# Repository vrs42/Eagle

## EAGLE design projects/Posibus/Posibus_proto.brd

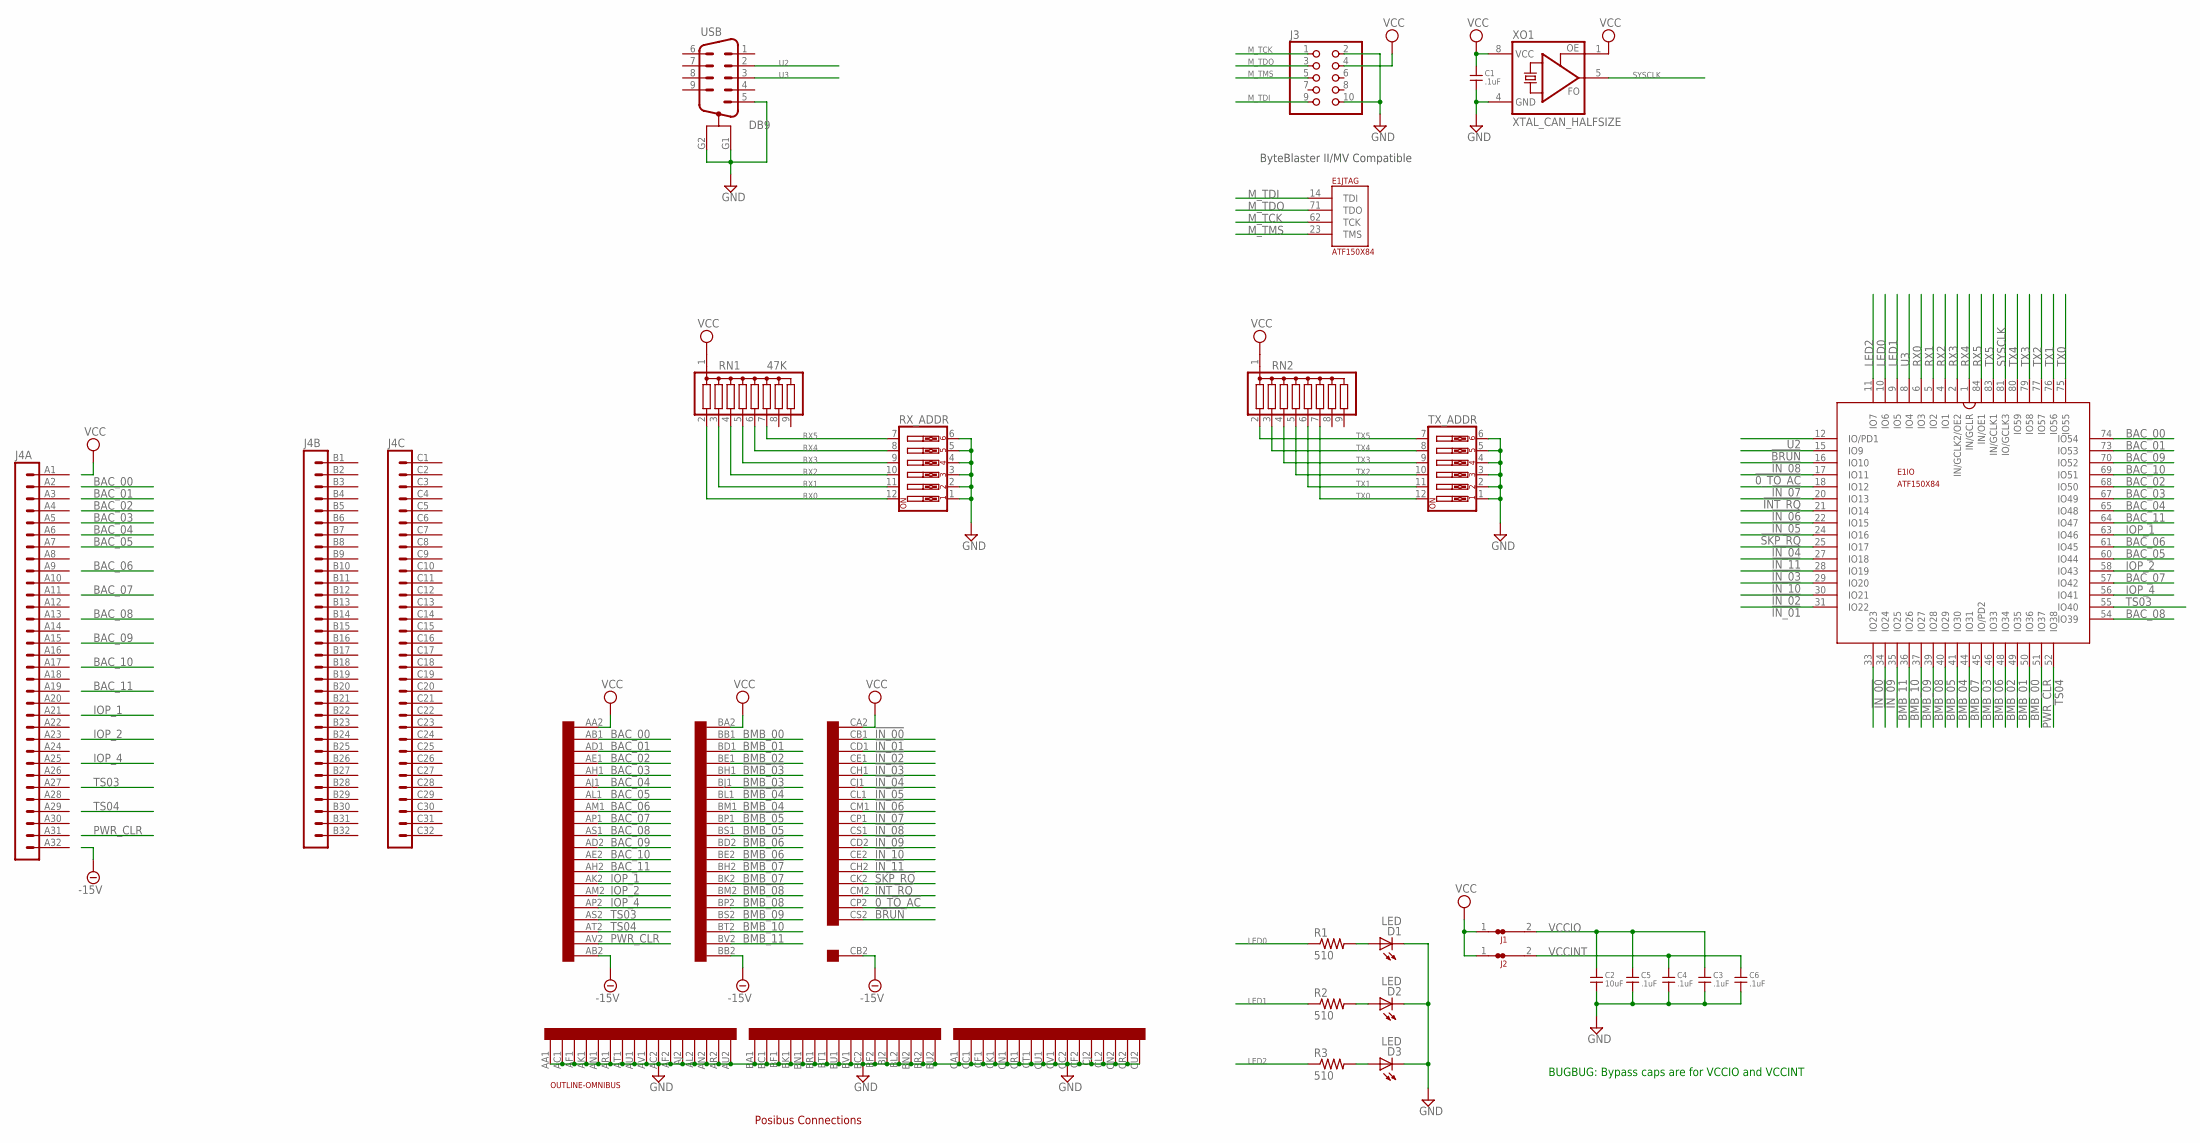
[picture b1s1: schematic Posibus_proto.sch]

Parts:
C1, C3, C4, C5, C6: .1uF; C_TH_5MM
C2: 10uF; C_TH_5MM
D1, D2, D3: LED; LED_TH_3MM
E1: ATF150X84; S84
J1, J2: JUMPER-NC1; NC1
J3: HDR_2X5"; HDR_2X5
J4: VG96-3B; VG96B
R1, R2, R3: 510; R_204/7
RN1: 47K; SIL9
RN2: G08R; SIL9
RX_ADDR: SW_DIP-6; EDG-06
TX_ADDR: SW_DIP-6; EDG-06
U$1: QUAD; EDGE-CON8
U$2: OUTLINE-OMNIBUS; OMNIBUS
USB: DB9; AMP_DB-9RA
XO1: XTAL_CAN_HALFSIZE

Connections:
!0_TO_AC: E1.17 (IO11), U$1.CP2
!BMB_03: U$1.BH1
!BMB_04: U$1.BL1
!BMB_05: U$1.BP1
!BMB_06: U$1.BD2
!BMB_07: U$1.BH2
!BMB_08: U$1.BM2
!BRUN: E1.15 (IO9), U$1.CS2
!INT_RQ: E1.20 (IO13), U$1.CM2
!IN_00: E1.33 (IO23), U$1.CB1
!IN_01: E1.31 (IO22), U$1.CD1
!IN_02: E1.30 (IO21), U$1.CE1
!IN_03: E1.28 (IO19), U$1.CH1
!IN_04: E1.25 (IO17), U$1.CJ1
!IN_05: E1.22 (IO15), U$1.CL1
!IN_06: E1.21 (IO14), U$1.CM1
!IN_07: E1.18 (IO12), U$1.CP1
!IN_08: E1.16 (IO10), U$1.CS1
!IN_09: E1.34 (IO24), U$1.CD2
!IN_10: E1.29 (IO20), U$1.CE2
!IN_11: E1.27 (IO18), U$1.CH2
!SKP_RQ: E1.24 (IO16), U$1.CK2
-15V: U$1.AB2, U$1.BB2, U$1.CB2
BAC_00: E1.74 (IO54), U$1.AB1
BAC_01: E1.73 (IO53), U$1.AD1
BAC_02: E1.68 (IO50), U$1.AE1
BAC_03: E1.67 (IO49), U$1.AH1
BAC_04: E1.65 (IO48), U$1.AJ1
BAC_05: E1.60 (IO44), U$1.AL1
BAC_06: E1.61 (IO45), U$1.AM1
BAC_07: E1.57 (IO42), U$1.AP1
BAC_08: E1.54 (IO39), U$1.AS1
BAC_09: E1.70 (IO52), U$1.AD2
BAC_10: E1.69 (IO51), U$1.AE2
BAC_11: E1.64 (IO47), U$1.AH2
BMB_00: E1.50 (IO36), U$1.BB1
BMB_01: E1.49 (IO35), U$1.BD1
BMB_02: E1.48 (IO34), U$1.BE1
BMB_03: E1.45 (IO/PD2), U$1.BJ1
BMB_04: E1.41 (IO30), U$1.BM1
BMB_05: E1.40 (IO29), U$1.BS1
BMB_06: E1.46 (IO33), U$1.BE2
BMB_07: E1.44 (IO31), U$1.BK2
BMB_08: E1.39 (IO28), U$1.BP2
BMB_09: E1.37 (IO27), U$1.BS2
BMB_10: E1.36 (IO26), U$1.BT2
BMB_11: E1.35 (IO25), U$1.BV2
GND: C1.2, C2.2, C3.2, C4.2, C5.2, C6.2, D1.K (C), D2.K (C), D3.K (C), E1.7 (GND), E1.19 (GND), E1.32 (GND), E1.42 (GND), E1.47 (GND), E1.59 (GND), E1.72 (GND), E1.82 (GND), J3.2, J3.10, RX_ADDR.1, RX_ADDR.2, RX_ADDR.3, RX_ADDR.4, RX_ADDR.5, RX_ADDR.6, TX_ADDR.1, TX_ADDR.2, TX_ADDR.3, TX_ADDR.4, TX_ADDR.5, TX_ADDR.6, U$1.AA1, U$1.AC1, U$1.AC2, U$1.AF1, U$1.AF2, U$1.AJ2, U$1.AK1, U$1.AL2, U$1.AN1, U$1.AN2, U$1.AR1, U$1.AR2, U$1.AT1, U$1.AU1, U$1.AU2, U$1.AV1, U$1.BA1, U$1.BC1, U$1.BC2, U$1.BF1, U$1.BF2, U$1.BJ2, U$1.BK1, U$1.BL2, U$1.BN1, U$1.BN2, U$1.BR1, U$1.BR2, U$1.BT1, U$1.BU1, U$1.BU2, U$1.BV1, U$1.CA1, U$1.CC1, U$1.CC2, U$1.CF1, U$1.CF2, U$1.CJ2, U$1.CK1, U$1.CL2, U$1.CN1, U$1.CN2, U$1.CR1, U$1.CR2, U$1.CT1, U$1.CU1, U$1.CU2, U$1.CV1, USB.5, USB.G1, USB.G2, XO1.4 (GND)
IOP_1: E1.63 (IO46), U$1.AK2
IOP_2: E1.58 (IO43), U$1.AM2
IOP_4: E1.56 (IO41), U$1.AP2
LED0: E1.10 (IO6), R1.1
LED1: E1.9 (IO5), R2.1
LED2: E1.11 (IO7), R3.1
M_TCK: E1.62 (TCK), J3.1
M_TDI: E1.14 (TDI), J3.9
M_TDO: E1.71 (TDO), J3.3
M_TMS: E1.23 (TMS), J3.5
unnamed: D3.A, R3.2
unnamed: D2.A, R2.2
unnamed: D1.A, R1.2
PWR_CLR: E1.51 (IO37), U$1.AV2
RX0: E1.6 (IO3), RN1.2, RX_ADDR.12
RX1: E1.5 (IO2), RN1.3, RX_ADDR.11
RX2: E1.4 (IO1), RN1.4, RX_ADDR.10
RX3: E1.2 (IN/GCLK2/OE2), RN1.5, RX_ADDR.9
RX4: E1.1 (IN/GCLR), RN1.6, RX_ADDR.8
RX5: E1.84 (IN/OE1), RN1.7, RX_ADDR.7
SYSCLK: E1.81 (IO/GCLK3), XO1.5 (FO)
TS03: E1.55 (IO40), U$1.AS2
TS04: E1.52 (IO38), U$1.AT2
TX0: E1.75 (IO55), RN2.7, TX_ADDR.12
TX1: E1.76 (IO56), RN2.6, TX_ADDR.11
TX2: E1.77 (IO57), RN2.5, TX_ADDR.10
TX3: E1.79 (IO58), RN2.4, TX_ADDR.9
TX4: E1.80 (IO59), RN2.3, TX_ADDR.8
TX5: E1.83 (IN/GCLK1), RN2.2, TX_ADDR.7
U2: E1.12 (IO/PD1), USB.2
U3: E1.8 (IO4), USB.3
VCC: C1.1, J1.1, J2.1, J3.4, RN1.1, RN2.1, U$1.AA2, U$1.BA2, U$1.CA2, XO1.1 (OE), XO1.8 (VCC)
VCCINT: C4.1, C6.1, E1.3 (VCCINT), E1.43 (VCCINT), J2.2
VCCIO: C2.1, C3.1, C5.1, E1.13 (VCCIO), E1.26 (VCCIO), E1.38 (VCCIO), E1.53 (VCCIO), E1.66 (VCCIO), E1.78 (VCCIO), J1.2

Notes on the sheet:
ByteBlaster II/MV Compatible
Posibus Connections
BUGBUG: Bypass caps are for VCCIO and VCCINT

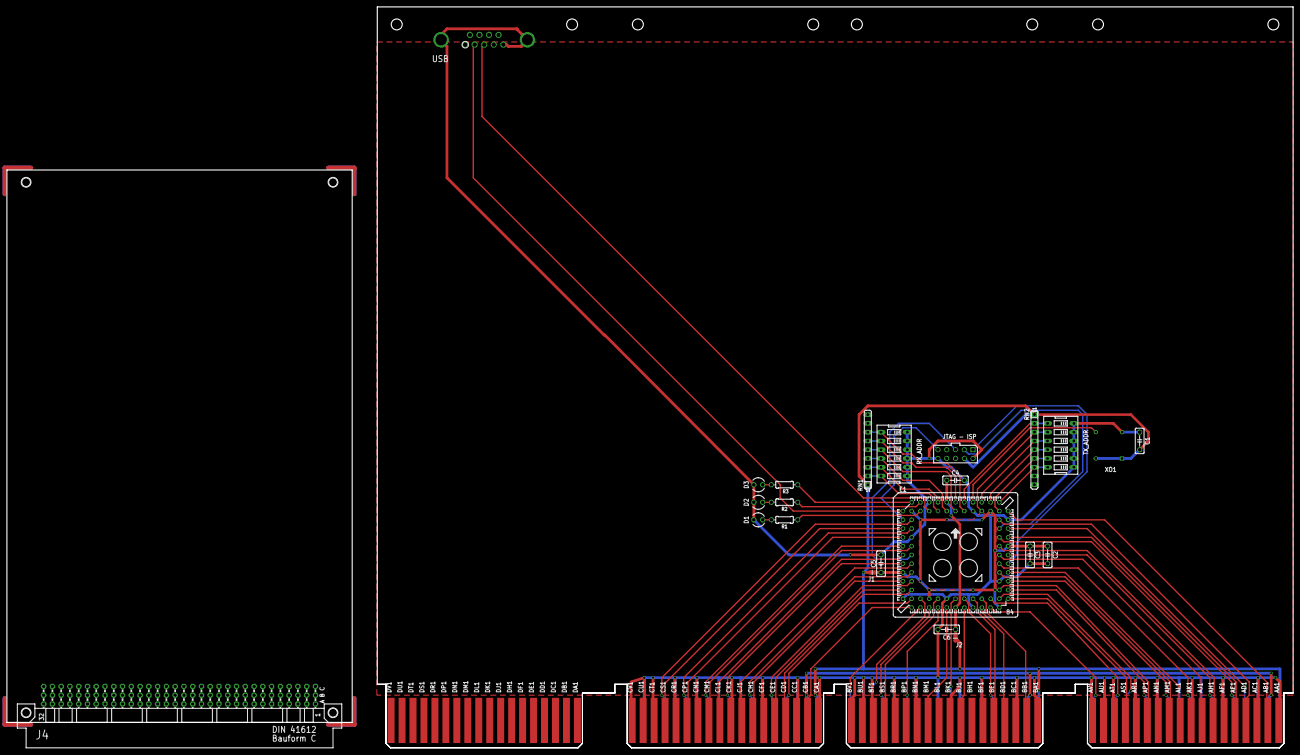
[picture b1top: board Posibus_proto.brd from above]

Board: 2 copper layers, 265.3 x 214.6 mm, 25 parts (0 on the bottom side), 76 nets.

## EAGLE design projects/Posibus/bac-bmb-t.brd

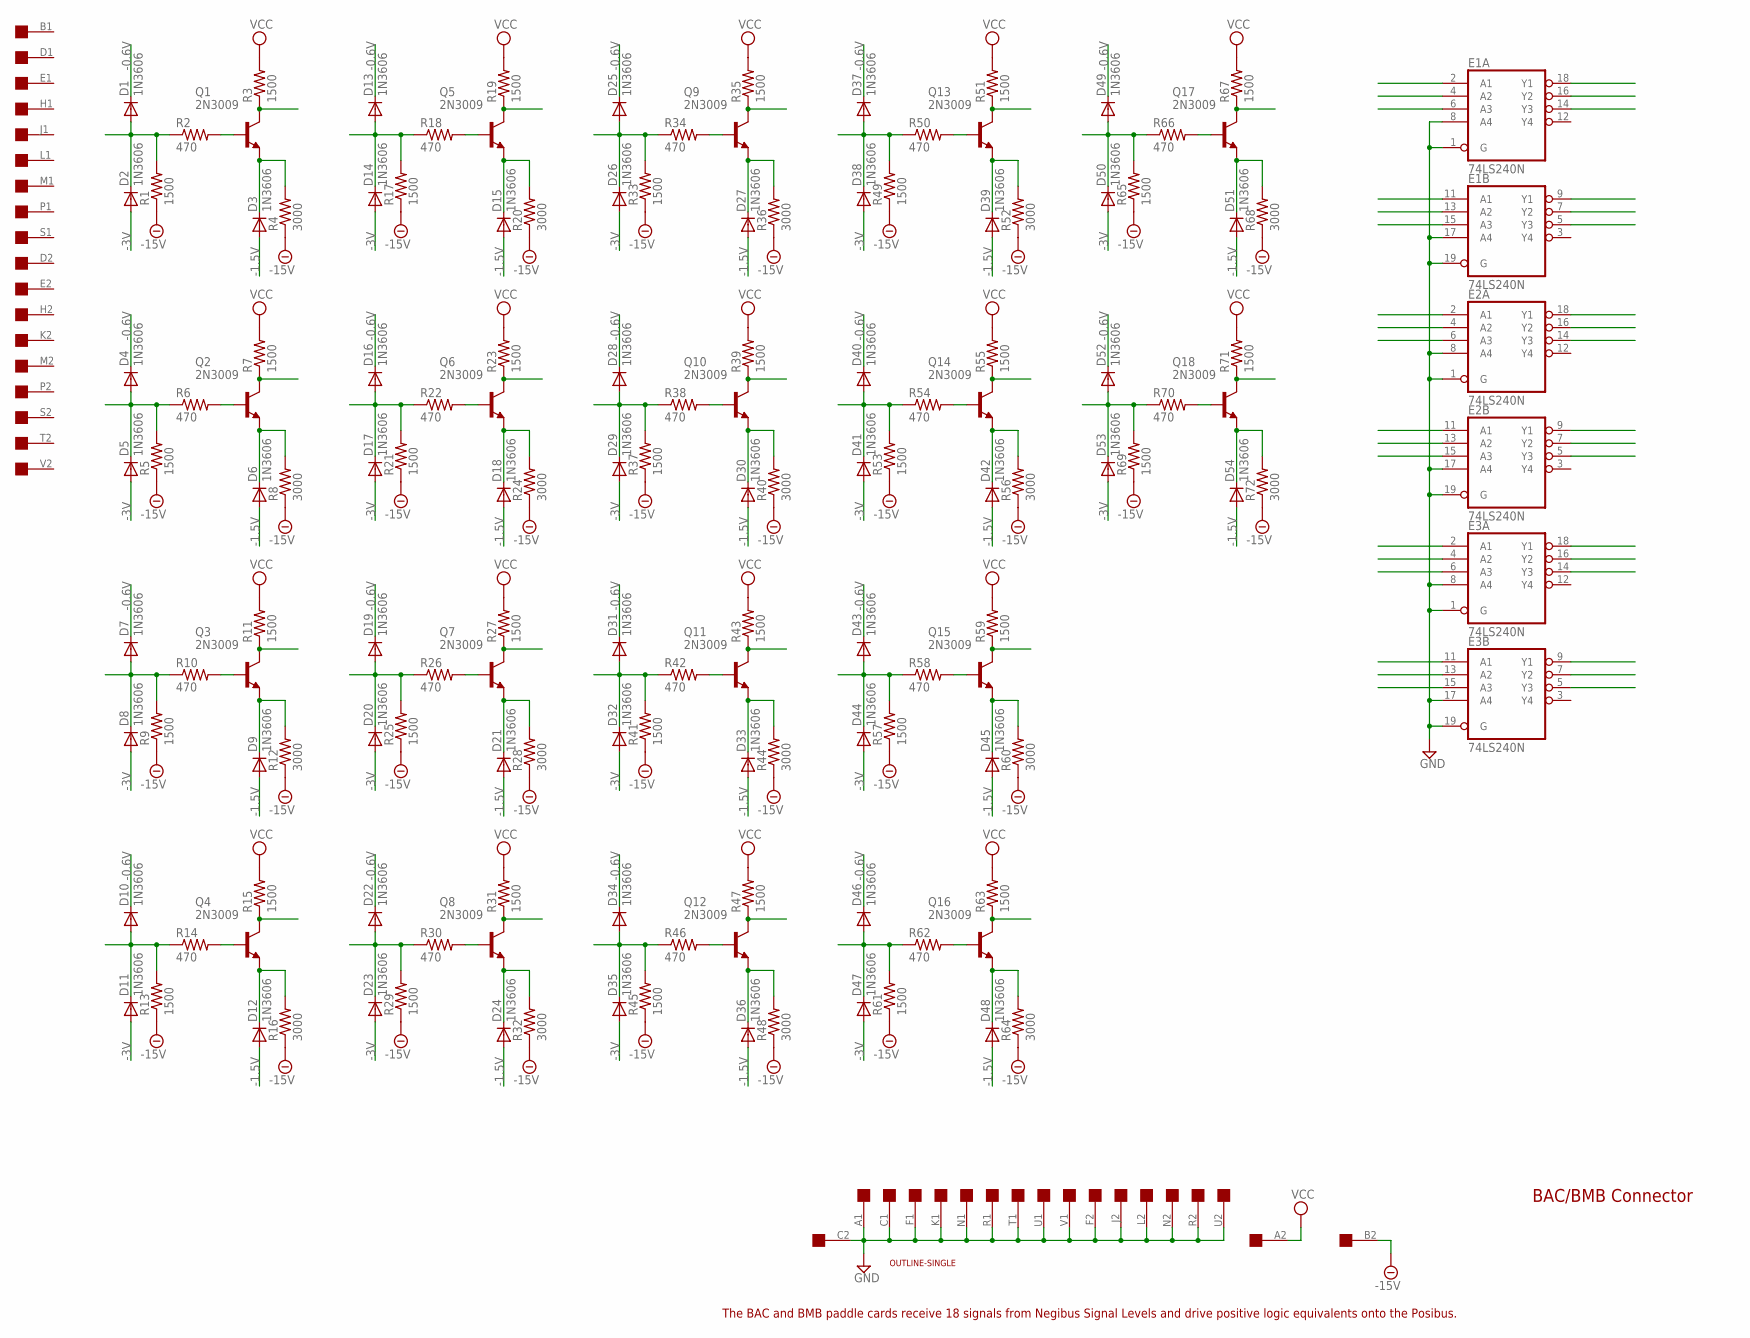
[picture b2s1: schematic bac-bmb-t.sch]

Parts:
D1, D2, D3, D4, D5, D6, D7, D8, D9, D10, D11, D12, D13, D14, D15, D16, D17, D18, D19, D20, D21, D22, D23, D24, D25, D26, D27, D28, D29, D30, D31, D32, D33, D34, D35, D36, D37, D38, D39, D40, D41, D42, D43, D44, D45, D46, D47, D48, D49, D50, D51, D52, D53, D54: 1N3606; DO35-10
E1, E2, E3: 74LS240N; DIL20
Q1, Q2, Q3, Q4, Q5, Q6, Q7, Q8, Q9, Q10, Q11, Q12, Q13, Q14, Q15, Q16, Q17, Q18: 2N3009; TO5
R1, R3, R5, R7, R9, R11, R13, R15, R17, R19, R21, R23, R25, R27, R29, R31, R33, R35, R37, R39, R41, R43, R45, R47, R49, R51, R53, R55, R57, R59, R61, R63, R65, R67, R69, R71: 1500; 0207/10
R2, R6, R10, R14, R18, R22, R26, R30, R34, R38, R42, R46, R50, R54, R58, R62, R66, R70: 470; 0207/10
R4, R8, R12, R16, R20, R24, R28, R32, R36, R40, R44, R48, R52, R56, R60, R64, R68, R72: 3000; 0207/10
U$1: SINGLE; EDGE-CON2
U$2: OUTLINE-SINGLE; SINGLE

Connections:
-0.6V: D1.C, D4.C, D7.C, D10.C, D13.C, D16.C, D19.C, D22.C, D25.C, D28.C, D31.C, D34.C, D37.C, D40.C, D43.C, D46.C, D49.C, D52.C
-1.5V: D3.A, D6.A, D9.A, D12.A, D15.A, D18.A, D21.A, D24.A, D27.A, D30.A, D33.A, D36.A, D39.A, D42.A, D45.A, D48.A, D51.A, D54.A
-3V: D2.A, D5.A, D8.A, D11.A, D14.A, D17.A, D20.A, D23.A, D26.A, D29.A, D32.A, D35.A, D38.A, D41.A, D44.A, D47.A, D50.A, D53.A
-15V: R1.1, R4.1, R5.1, R8.1, R9.1, R12.1, R13.1, R16.1, R17.1, R20.1, R21.1, R24.1, R25.1, R28.1, R29.1, R32.1, R33.1, R36.1, R37.1, R40.1, R41.1, R44.1, R45.1, R48.1, R49.1, R52.1, R53.1, R56.1, R57.1, R60.1, R61.1, R64.1, R65.1, R68.1, R69.1, R72.1, U$1.B2
GND: E1.1 (G), E1.8 (A4), E1.10 (GND), E1.17 (A4), E1.19 (G), E2.1 (G), E2.8 (A4), E2.10 (GND), E2.17 (A4), E2.19 (G), E3.1 (G), E3.8 (A4), E3.10 (GND), E3.17 (A4), E3.19 (G), U$1.A1, U$1.C1, U$1.C2, U$1.F1, U$1.F2, U$1.J2, U$1.K1, U$1.L2, U$1.N1, U$1.N2, U$1.R1, U$1.R2, U$1.T1, U$1.U1, U$1.U2, U$1.V1
unnamed: D1.A, D2.C, R1.2, R2.1
unnamed: Q1.2 (B), R2.2
unnamed: D3.C, Q1.1 (E), R4.2
unnamed: Q1.3 (C), R3.1
unnamed: D4.A, D5.C, R5.2, R6.1
unnamed: Q2.2 (B), R6.2
unnamed: D6.C, Q2.1 (E), R8.2
unnamed: Q2.3 (C), R7.1
unnamed: D7.A, D8.C, R9.2, R10.1
unnamed: Q3.2 (B), R10.2
unnamed: D9.C, Q3.1 (E), R12.2
unnamed: Q3.3 (C), R11.1
unnamed: D10.A, D11.C, R13.2, R14.1
unnamed: Q4.2 (B), R14.2
unnamed: D12.C, Q4.1 (E), R16.2
unnamed: Q4.3 (C), R15.1
unnamed: D13.A, D14.C, R17.2, R18.1
unnamed: Q5.2 (B), R18.2
unnamed: D15.C, Q5.1 (E), R20.2
unnamed: Q5.3 (C), R19.1
unnamed: D16.A, D17.C, R21.2, R22.1
unnamed: Q6.2 (B), R22.2
unnamed: D18.C, Q6.1 (E), R24.2
unnamed: Q6.3 (C), R23.1
unnamed: D19.A, D20.C, R25.2, R26.1
unnamed: Q7.2 (B), R26.2
unnamed: D21.C, Q7.1 (E), R28.2
unnamed: Q7.3 (C), R27.1
unnamed: D22.A, D23.C, R29.2, R30.1
unnamed: Q8.2 (B), R30.2
unnamed: D24.C, Q8.1 (E), R32.2
unnamed: Q8.3 (C), R31.1
unnamed: D25.A, D26.C, R33.2, R34.1
unnamed: Q9.2 (B), R34.2
unnamed: D27.C, Q9.1 (E), R36.2
unnamed: Q9.3 (C), R35.1
unnamed: D28.A, D29.C, R37.2, R38.1
unnamed: Q10.2 (B), R38.2
unnamed: D30.C, Q10.1 (E), R40.2
unnamed: Q10.3 (C), R39.1
unnamed: D31.A, D32.C, R41.2, R42.1
unnamed: Q11.2 (B), R42.2
unnamed: D33.C, Q11.1 (E), R44.2
unnamed: Q11.3 (C), R43.1
unnamed: D34.A, D35.C, R45.2, R46.1
unnamed: Q12.2 (B), R46.2
unnamed: D36.C, Q12.1 (E), R48.2
unnamed: Q12.3 (C), R47.1
unnamed: D37.A, D38.C, R49.2, R50.1
unnamed: Q13.2 (B), R50.2
unnamed: D39.C, Q13.1 (E), R52.2
unnamed: Q13.3 (C), R51.1
unnamed: D40.A, D41.C, R53.2, R54.1
unnamed: Q14.2 (B), R54.2
unnamed: D42.C, Q14.1 (E), R56.2
unnamed: Q14.3 (C), R55.1
unnamed: D43.A, D44.C, R57.2, R58.1
unnamed: Q15.2 (B), R58.2
unnamed: D45.C, Q15.1 (E), R60.2
unnamed: Q15.3 (C), R59.1
unnamed: D46.A, D47.C, R61.2, R62.1
unnamed: Q16.2 (B), R62.2
unnamed: D48.C, Q16.1 (E), R64.2
unnamed: Q16.3 (C), R63.1
unnamed: D49.A, D50.C, R65.2, R66.1
unnamed: Q17.2 (B), R66.2
unnamed: D51.C, Q17.1 (E), R68.2
unnamed: Q17.3 (C), R67.1
unnamed: D52.A, D53.C, R69.2, R70.1
unnamed: Q18.2 (B), R70.2
unnamed: D54.C, Q18.1 (E), R72.2
unnamed: Q18.3 (C), R71.1
VCC: E1.20 (VCC), E2.20 (VCC), E3.20 (VCC), R3.2, R7.2, R11.2, R15.2, R19.2, R23.2, R27.2, R31.2, R35.2, R39.2, R43.2, R47.2, R51.2, R55.2, R59.2, R63.2, R67.2, R71.2, U$1.A2

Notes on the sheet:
BAC/BMB Connector
The BAC and BMB paddle cards receive 18 signals from Negibus Signal Levels and drive positive logic equivalents onto the Posibus.

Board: 2 copper layers, 149 parts (0 on the bottom side), 78 nets, no tracks yet.

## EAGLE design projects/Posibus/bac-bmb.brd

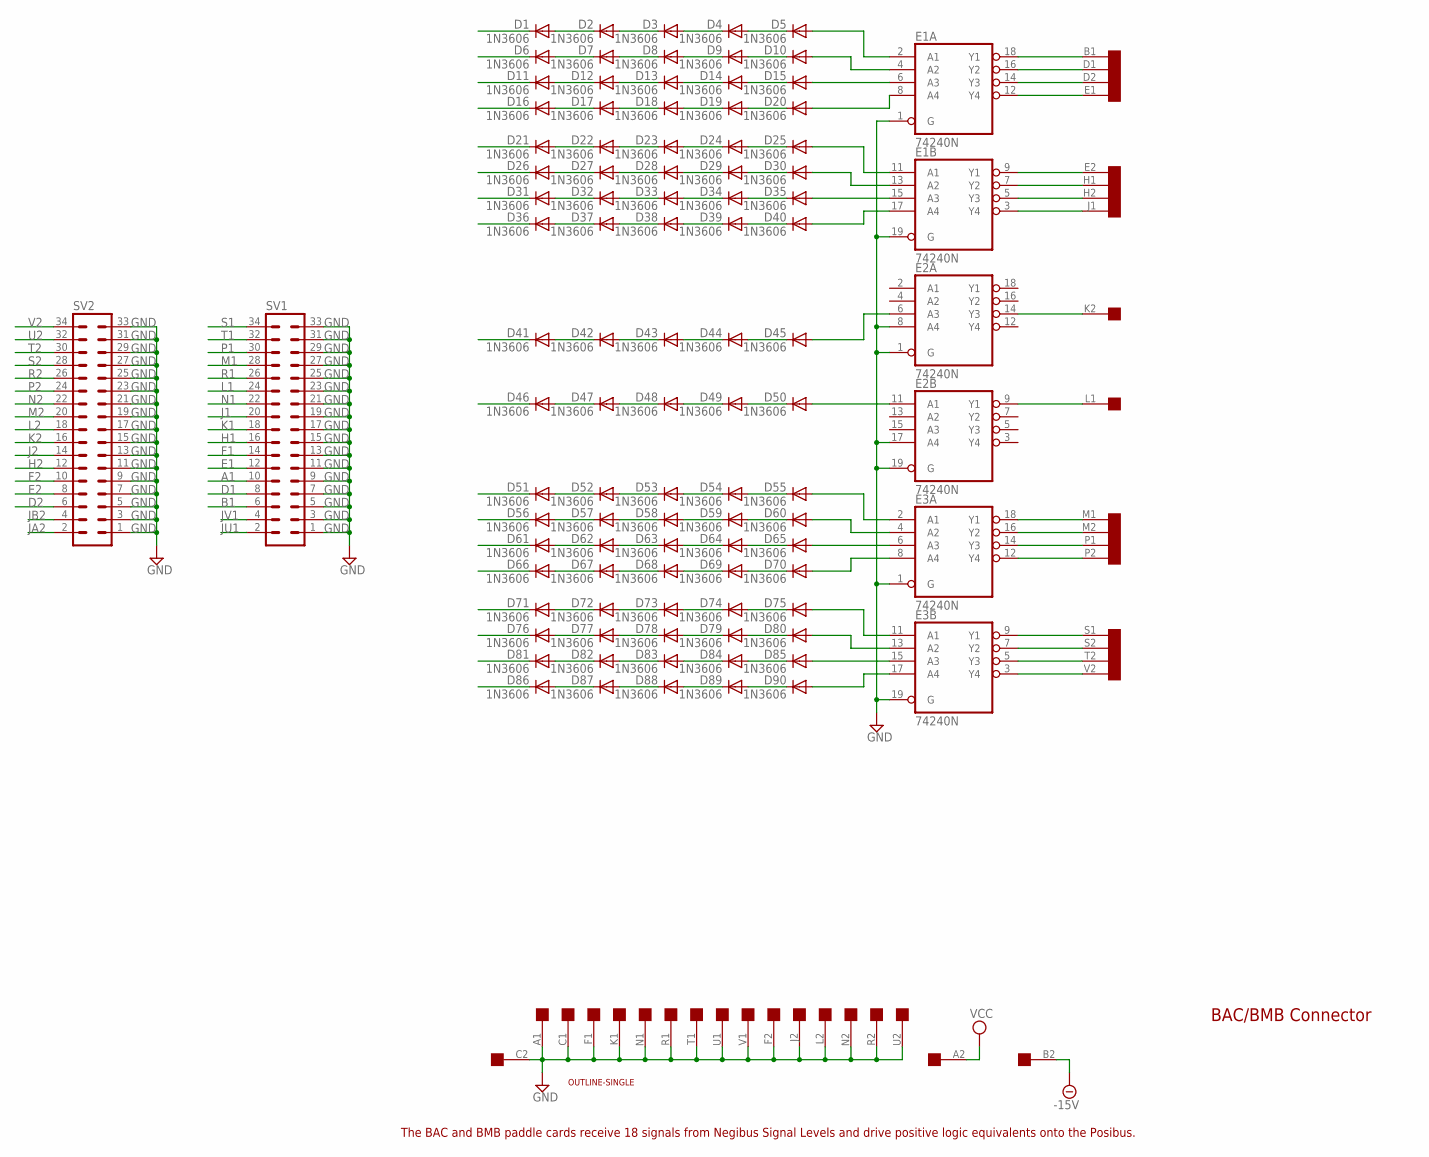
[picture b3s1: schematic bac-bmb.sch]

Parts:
D1, D2, D3, D4, D5, D6, D7, D8, D9, D10, D11, D12, D13, D14, D15, D16, D17, D18, D19, D20, D21, D22, D23, D24, D25, D26, D27, D28, D29, D30, D31, D32, D33, D34, D35, D36, D37, D38, D39, D40, D41, D42, D43, D44, D45, D46, D47, D48, D49, D50, D51, D52, D53, D54, D55, D56, D57, D58, D59, D60, D61, D62, D63, D64, D65, D66, D67, D68, D69, D70, D71, D72, D73, D74, D75, D76, D77, D78, D79, D80, D81, D82, D83, D84, D85, D86, D87, D88, D89, D90: 1N3606; DO35-10
E1, E2, E3: 74240N; DIL20
SV1, SV2: MA17-2
U$1: SINGLE; EDGE-CON2
U$2: OUTLINE-SINGLE; SINGLE

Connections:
-15V: U$1.B2
A1: SV1.10
B1: D1.C, SV1.6
D1: D6.C, SV1.8
D2: D11.C, SV2.6
E1: D16.C, SV1.12
E2: D21.C, SV2.8
F1: SV1.14
F2: SV2.10
GND: E1.1 (G), E1.10 (GND), E1.19 (G), E2.1 (G), E2.8 (A4), E2.10 (GND), E2.17 (A4), E2.19 (G), E3.1 (G), E3.10 (GND), E3.19 (G), SV1.1, SV1.3, SV1.5, SV1.7, SV1.9, SV1.11, SV1.13, SV1.15, SV1.17, SV1.19, SV1.21, SV1.23, SV1.25, SV1.27, SV1.29, SV1.31, SV1.33, SV2.1, SV2.3, SV2.5, SV2.7, SV2.9, SV2.11, SV2.13, SV2.15, SV2.17, SV2.19, SV2.21, SV2.23, SV2.25, SV2.27, SV2.29, SV2.31, SV2.33, U$1.A1, U$1.C1, U$1.C2, U$1.F1, U$1.F2, U$1.J2, U$1.K1, U$1.L2, U$1.N1, U$1.N2, U$1.R1, U$1.R2, U$1.T1, U$1.U1, U$1.U2, U$1.V1
H1: D26.C, SV1.16
H2: D31.C, SV2.12
J1: D36.C, SV1.20
J2: SV2.14
JA2: SV2.2
JB2: SV2.4
JU1: SV1.2
JV1: SV1.4
K1: SV1.18
K2: D41.C, SV2.16
L1: D46.C, SV1.24
L2: SV2.18
M1: D51.C, SV1.28
M2: D56.C, SV2.20
N1: SV1.22
N2: SV2.22
unnamed: D1.A, D2.C
unnamed: D2.A, D3.C
unnamed: D3.A, D4.C
unnamed: D4.A, D5.C
unnamed: D6.A, D7.C
unnamed: D7.A, D8.C
unnamed: D8.A, D9.C
unnamed: D9.A, D10.C
unnamed: D11.A, D12.C
unnamed: D12.A, D13.C
unnamed: D13.A, D14.C
unnamed: D14.A, D15.C
unnamed: D16.A, D17.C
unnamed: D17.A, D18.C
unnamed: D18.A, D19.C
unnamed: D19.A, D20.C
unnamed: D21.A, D22.C
unnamed: D22.A, D23.C
unnamed: D23.A, D24.C
unnamed: D24.A, D25.C
unnamed: D26.A, D27.C
unnamed: D27.A, D28.C
unnamed: D28.A, D29.C
unnamed: D29.A, D30.C
unnamed: D31.A, D32.C
unnamed: D32.A, D33.C
unnamed: D33.A, D34.C
unnamed: D34.A, D35.C
unnamed: D36.A, D37.C
unnamed: D37.A, D38.C
unnamed: D38.A, D39.C
unnamed: D39.A, D40.C
unnamed: D41.A, D42.C
unnamed: D42.A, D43.C
unnamed: D43.A, D44.C
unnamed: D44.A, D45.C
unnamed: D46.A, D47.C
unnamed: D47.A, D48.C
unnamed: D48.A, D49.C
unnamed: D49.A, D50.C
unnamed: D51.A, D52.C
unnamed: D52.A, D53.C
unnamed: D53.A, D54.C
unnamed: D54.A, D55.C
unnamed: D56.A, D57.C
unnamed: D57.A, D58.C
unnamed: D58.A, D59.C
unnamed: D59.A, D60.C
unnamed: D61.A, D62.C
unnamed: D62.A, D63.C
unnamed: D63.A, D64.C
unnamed: D64.A, D65.C
unnamed: D66.A, D67.C
unnamed: D67.A, D68.C
unnamed: D68.A, D69.C
unnamed: D69.A, D70.C
unnamed: D71.A, D72.C
unnamed: D72.A, D73.C
unnamed: D73.A, D74.C
unnamed: D74.A, D75.C
unnamed: D76.A, D77.C
unnamed: D77.A, D78.C
unnamed: D78.A, D79.C
unnamed: D79.A, D80.C
unnamed: D81.A, D82.C
unnamed: D82.A, D83.C
unnamed: D83.A, D84.C
unnamed: D84.A, D85.C
unnamed: D86.A, D87.C
unnamed: D87.A, D88.C
unnamed: D88.A, D89.C
unnamed: D89.A, D90.C
unnamed: D10.A, E1.4 (A2)
unnamed: D85.A, E3.15 (A3)
unnamed: D5.A, E1.2 (A1)
unnamed: D15.A, E1.6 (A3)
unnamed: D20.A, E1.8 (A4)
unnamed: D25.A, E1.11 (A1)
unnamed: D30.A, E1.13 (A2)
unnamed: D35.A, E1.15 (A3)
unnamed: D40.A, E1.17 (A4)
unnamed: D45.A, E2.6 (A3)
unnamed: D50.A, E2.11 (A1)
unnamed: D55.A, E3.2 (A1)
unnamed: D60.A, E3.4 (A2)
unnamed: D65.A, E3.6 (A3)
unnamed: D70.A, E3.8 (A4)
unnamed: D75.A, E3.11 (A1)
unnamed: D80.A, E3.13 (A2)
unnamed: D90.A, E3.17 (A4)
unnamed: E3.5 (Y3), U$1.T2
unnamed: E1.18 (Y1), U$1.B1
unnamed: E1.16 (Y2), U$1.D1
unnamed: E1.14 (Y3), U$1.D2
unnamed: E1.12 (Y4), U$1.E1
unnamed: E1.9 (Y1), U$1.E2
unnamed: E1.7 (Y2), U$1.H1
unnamed: E1.5 (Y3), U$1.H2
unnamed: E1.3 (Y4), U$1.J1
unnamed: E2.14 (Y3), U$1.K2
unnamed: E2.9 (Y1), U$1.L1
unnamed: E3.18 (Y1), U$1.M1
unnamed: E3.16 (Y2), U$1.M2
unnamed: E3.14 (Y3), U$1.P1
unnamed: E3.12 (Y4), U$1.P2
unnamed: E3.9 (Y1), U$1.S1
unnamed: E3.7 (Y2), U$1.S2
unnamed: E3.3 (Y4), U$1.V2
P1: D61.C, SV1.30
P2: D66.C, SV2.24
R1: SV1.26
R2: SV2.26
S1: D71.C, SV1.34
S2: D76.C, SV2.28
T1: SV1.32
T2: D81.C, SV2.30
U2: SV2.32
V2: D86.C, SV2.34
VCC: E1.20 (VCC), E2.20 (VCC), E3.20 (VCC), U$1.A2

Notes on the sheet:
BAC/BMB Connector
The BAC and BMB paddle cards receive 18 signals from Negibus Signal Levels and drive positive logic equivalents onto the Posibus.

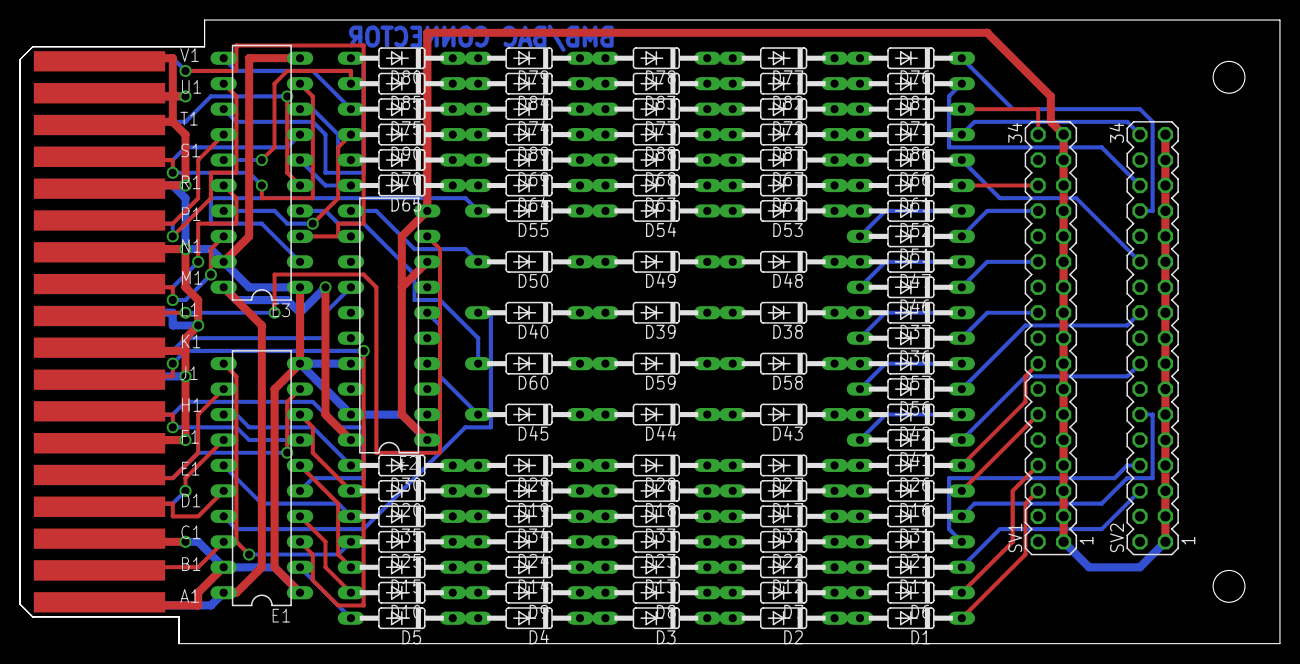
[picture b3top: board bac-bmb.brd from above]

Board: 2 copper layers, 125.7 x 62.2 mm, 97 parts (0 on the bottom side), 128 nets.

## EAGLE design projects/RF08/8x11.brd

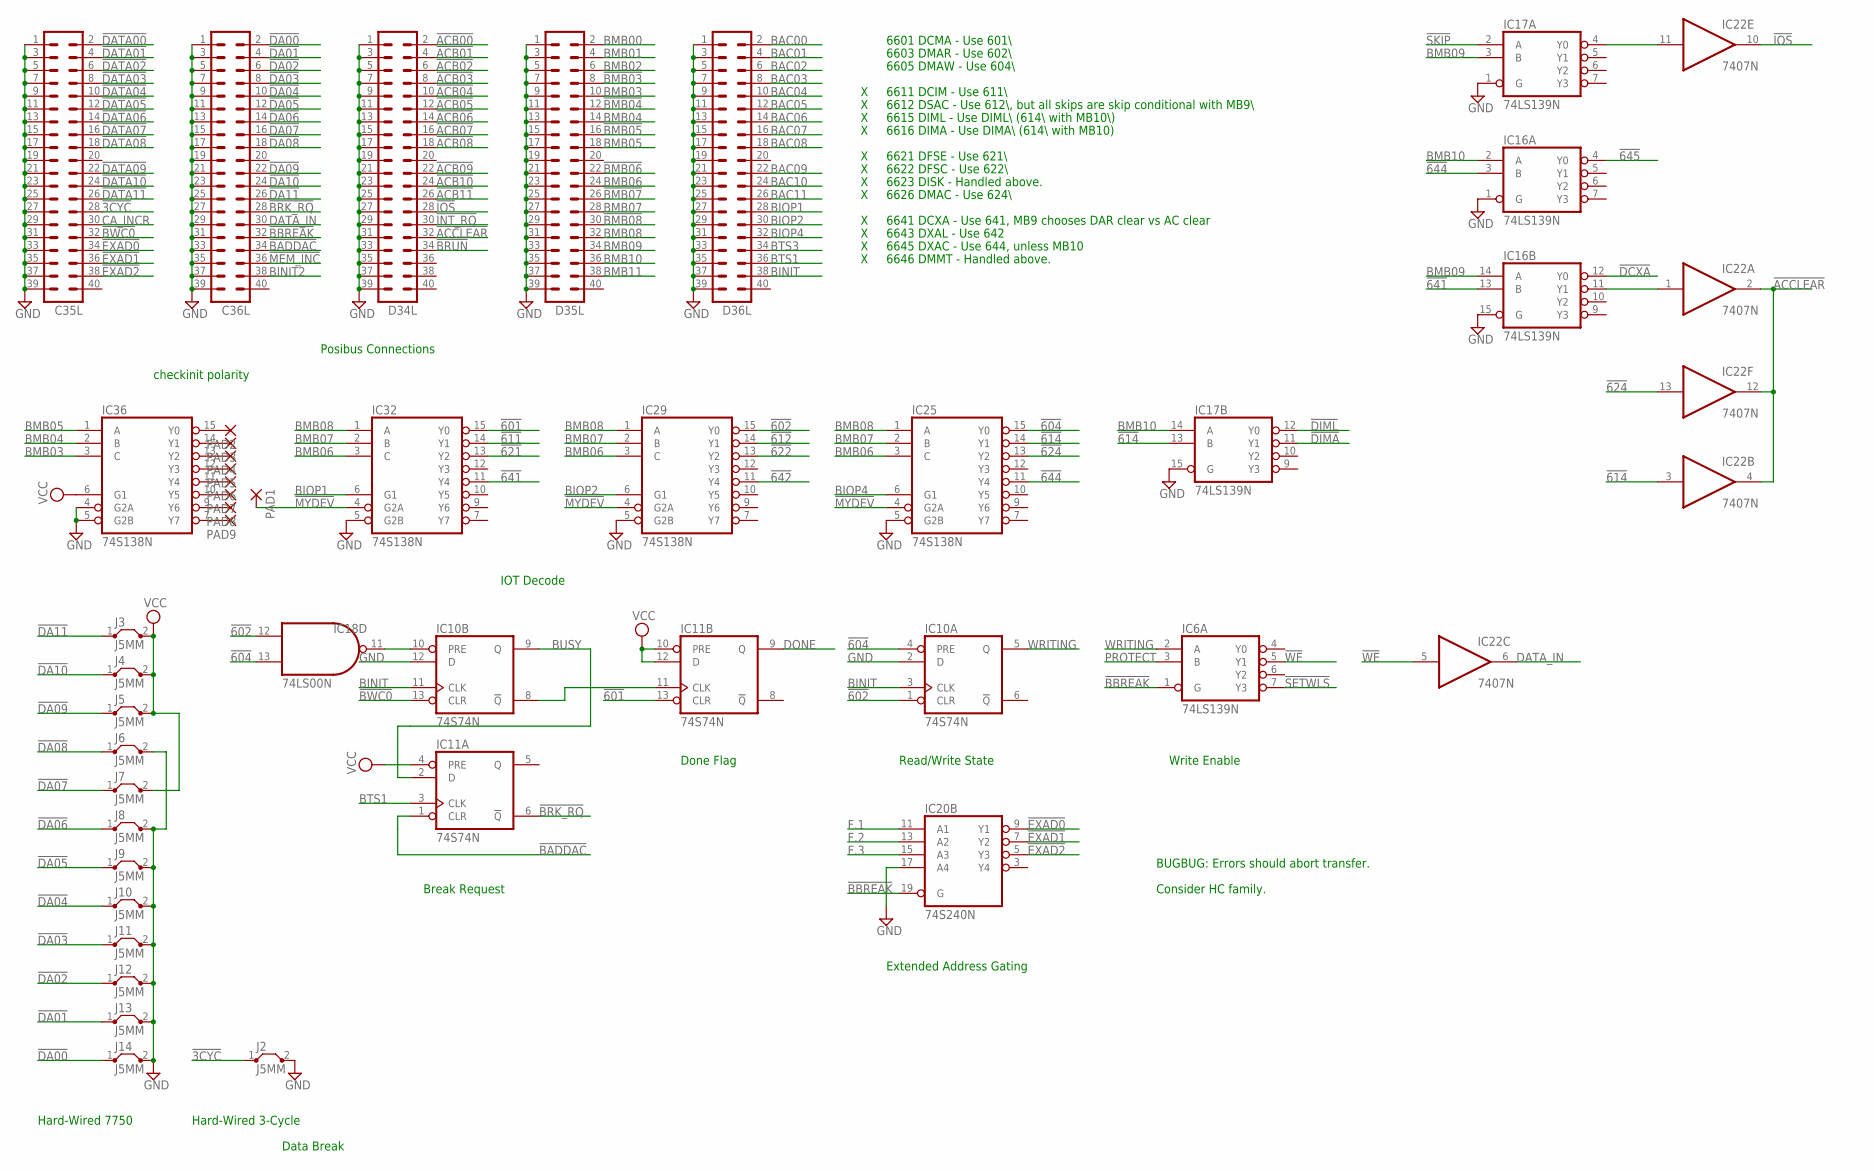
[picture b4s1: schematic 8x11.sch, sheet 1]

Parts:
C35L, C36L: MA20-2
D34L, D35L, D36L: MA20-2
IC6, IC16, IC17: 74LS139N; DIL16
IC10, IC11: 74S74N; DIL14
IC18: 74LS00N; DIL14
IC20: 74S240N; DIL20
IC22: 7407N; DIL14
IC25, IC29, IC32, IC36: 74S138N; DIL16
J2, J3, J4, J5, J6, J7, J8, J9, J10, J11, J12, J13, J14: J5MM; 05
PAD1, PAD2, PAD3, PAD4, PAD5, PAD6, PAD7, PAD8, PAD9: 1,6/0,8

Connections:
!3CYC: C35L.28, J2.1
!601: IC11.13 (CLR), IC32.15 (Y0); also elsewhere on the board
!602: IC10.1 (CLR), IC18.12 (I0), IC29.15 (Y0); also elsewhere on the board
!604: IC10.4 (PRE), IC18.13 (I1), IC25.15 (Y0); also elsewhere on the board
!611: IC32.14 (Y1); also elsewhere on the board
!612: IC29.14 (Y1); also elsewhere on the board
!614: IC17.13 (B), IC22.3 (I), IC25.14 (Y1)
!621: IC32.13 (Y2); also elsewhere on the board
!622: IC29.13 (Y2); also elsewhere on the board
!624: IC22.13 (I), IC25.13 (Y2); also elsewhere on the board
!641: IC16.13 (B), IC32.11 (Y4)
!642: IC29.11 (Y4); also elsewhere on the board
!644: IC16.3 (B), IC25.11 (Y4)
!645: IC16.4 (Y0); also elsewhere on the board
!ACB00: D34L.2; also elsewhere on the board
!ACB01: D34L.4; also elsewhere on the board
!ACB02: D34L.6; also elsewhere on the board
!ACB03: D34L.8; also elsewhere on the board
!ACB04: D34L.10; also elsewhere on the board
!ACB05: D34L.12; also elsewhere on the board
!ACB06: D34L.14; also elsewhere on the board
!ACB07: D34L.16; also elsewhere on the board
!ACB08: D34L.18; also elsewhere on the board
!ACB09: D34L.22; also elsewhere on the board
!ACB10: D34L.24; also elsewhere on the board
!ACB11: D34L.26; also elsewhere on the board
!ACCLEAR: D34L.32, IC22.2 (O), IC22.4 (O), IC22.12 (O)
!BADDAC: C36L.34, IC11.1 (CLR)
!BBREAK: C36L.32, IC6.1 (G), IC20.19 (G); also elsewhere on the board
!BMB03: D35L.8
!BMB04: D35L.12
!BMB05: D35L.16
!BMB06: D35L.22
!BMB07: D35L.26
!BMB08: D35L.30
!BRK_RQ: C36L.28, IC11.6 (!Q); also elsewhere on the board
!BRUN: D34L.34
!BWC0: C35L.32, IC10.13 (CLR); also elsewhere on the board
!DA00: C36L.2, J14.1
!DA01: C36L.4, J13.1
!DA02: C36L.6, J12.1
!DA03: C36L.8, J11.1
!DA04: C36L.10, J10.1
!DA05: C36L.12, J9.1
!DA06: C36L.14, J8.1
!DA07: C36L.16, J7.1
!DA08: C36L.18, J6.1
!DA09: C36L.22, J5.1
!DA10: C36L.24, J4.1
!DA11: C36L.26, J3.1
!DATA00: C35L.2; also elsewhere on the board
!DATA01: C35L.4; also elsewhere on the board
!DATA02: C35L.6; also elsewhere on the board
!DATA03: C35L.8; also elsewhere on the board
!DATA04: C35L.10; also elsewhere on the board
!DATA05: C35L.12; also elsewhere on the board
!DATA06: C35L.14; also elsewhere on the board
!DATA07: C35L.16; also elsewhere on the board
!DATA08: C35L.18; also elsewhere on the board
!DATA09: C35L.22; also elsewhere on the board
!DATA10: C35L.24; also elsewhere on the board
!DATA11: C35L.26; also elsewhere on the board
!DCXA: IC16.12 (Y0); also elsewhere on the board
!DIMA: IC17.11 (Y1); also elsewhere on the board
!DIML: IC17.12 (Y0); also elsewhere on the board
!EXAD0: C35L.34, IC20.9 (Y1)
!EXAD1: C35L.36, IC20.7 (Y2)
!EXAD2: C35L.38, IC20.5 (Y3)
!INT_RQ: D34L.30; also elsewhere on the board
!IOS: D34L.28, IC22.10 (O)
!MEM_INC: C36L.36
!MYDEV: IC25.4 (G2A), IC29.4 (G2A), IC32.4 (G2A), PAD1.1
!SETWLS: IC6.7 (Y3); also elsewhere on the board
!SKIP: IC17.2 (A); also elsewhere on the board
!WE: IC6.5 (Y1), IC22.5 (I); also elsewhere on the board
BAC00: D36L.2; also elsewhere on the board
BAC01: D36L.4; also elsewhere on the board
BAC02: D36L.6; also elsewhere on the board
BAC03: D36L.8; also elsewhere on the board
BAC04: D36L.10; also elsewhere on the board
BAC05: D36L.12; also elsewhere on the board
BAC06: D36L.14; also elsewhere on the board
BAC07: D36L.16; also elsewhere on the board
BAC08: D36L.18; also elsewhere on the board
BAC09: D36L.22; also elsewhere on the board
BAC10: D36L.24; also elsewhere on the board
BAC11: D36L.26; also elsewhere on the board
BINIT: D36L.38, IC10.3 (CLK), IC10.11 (CLK); also elsewhere on the board
BINIT2: C36L.38
BIOP1: D36L.28, IC32.6 (G1)
BIOP2: D36L.30, IC29.6 (G1)
BIOP4: D36L.32, IC25.6 (G1)
BMB00: D35L.2; also elsewhere on the board
BMB01: D35L.4; also elsewhere on the board
BMB02: D35L.6; also elsewhere on the board
BMB03: D35L.10, IC36.3 (C); also elsewhere on the board
BMB04: D35L.14, IC36.2 (B); also elsewhere on the board
BMB05: D35L.18, IC36.1 (A); also elsewhere on the board
BMB06: D35L.24, IC25.3 (C), IC29.3 (C), IC32.3 (C); also elsewhere on the board
BMB07: D35L.28, IC25.2 (B), IC29.2 (B), IC32.2 (B); also elsewhere on the board
BMB08: D35L.32, IC25.1 (A), IC29.1 (A), IC32.1 (A); also elsewhere on the board
BMB09: D35L.34, IC16.14 (A), IC17.3 (B); also elsewhere on the board
BMB10: D35L.36, IC16.2 (A), IC17.14 (A); also elsewhere on the board
BMB11: D35L.38; also elsewhere on the board
BTS1: D36L.36, IC11.3 (CLK)
BTS3: D36L.34
BUSY: IC10.9 (Q), IC11.2 (D); also elsewhere on the board
CA_INCR: C35L.30
DATA_IN: C36L.30, IC22.6 (O)
DONE: IC11.9 (Q); also elsewhere on the board
F.1: IC20.11 (A1); also elsewhere on the board
F.2: IC20.13 (A2); also elsewhere on the board
F.3: IC20.15 (A3); also elsewhere on the board
GND: C35L.1, C35L.3, C35L.5, C35L.7, C35L.9, C35L.11, C35L.13, C35L.15, C35L.17, C35L.19, C35L.21, C35L.23, C35L.25, C35L.27, C35L.29, C35L.31, C35L.33, C35L.35, C35L.37, C35L.39, C36L.1, C36L.3, C36L.5, C36L.7, C36L.9, C36L.11, C36L.13, C36L.15, C36L.17, C36L.19, C36L.21, C36L.23, C36L.25, C36L.27, C36L.29, C36L.31, C36L.33, C36L.35, C36L.37, C36L.39, D34L.1, D34L.3, D34L.5, D34L.7, D34L.9, D34L.11, D34L.13, D34L.15, D34L.17, D34L.19, D34L.21, D34L.23, D34L.25, D34L.27, D34L.29, D34L.31, D34L.33, D34L.35, D34L.37, D34L.39, D35L.1, D35L.3, D35L.5, D35L.7, D35L.9, D35L.11, D35L.13, D35L.15, D35L.17, D35L.19, D35L.21, D35L.23, D35L.25, D35L.27, D35L.29, D35L.31, D35L.33, D35L.35, D35L.37, D35L.39, D36L.1, D36L.3, D36L.5, D36L.7, D36L.9, D36L.11, D36L.13, D36L.15, D36L.17, D36L.19, D36L.21, D36L.23, D36L.25, D36L.27, D36L.29, D36L.31, D36L.33, D36L.35, D36L.37, D36L.39, IC6.8 (GND), IC10.2 (D), IC10.7 (GND), IC10.12 (D), IC11.7 (GND), IC16.1 (G), IC16.8 (GND), IC16.15 (G), IC17.1 (G), IC17.8 (GND), IC17.15 (G), IC18.7 (GND), IC20.10 (GND), IC20.17 (A4), IC22.7 (GND), IC25.5 (G2B), IC25.8 (GND), IC29.5 (G2B), IC29.8 (GND), IC32.5 (G2B), IC32.8 (GND), IC36.4 (G2A), IC36.5 (G2B), IC36.8 (GND), J2.2, J6.2, J8.2, J9.2, J10.2, J11.2, J12.2, J13.2, J14.2; also elsewhere on the board
unnamed: IC36.9 (Y6), PAD8.1
unnamed: IC10.8 (!Q), IC11.11 (CLK)
unnamed: IC36.15 (Y0), PAD2.1
unnamed: IC36.14 (Y1), PAD3.1
unnamed: IC36.13 (Y2), PAD4.1
unnamed: IC36.12 (Y3), PAD5.1
unnamed: IC36.11 (Y4), PAD6.1
unnamed: IC36.10 (Y5), PAD7.1
unnamed: IC36.7 (Y7), PAD9.1
unnamed: IC16.11 (Y1), IC22.1 (I)
unnamed: IC17.4 (Y0), IC22.11 (I)
unnamed: IC10.10 (PRE), IC18.11 (O)
PROTECT: IC6.3 (B); also elsewhere on the board
VCC: IC6.16 (VCC), IC10.14 (VCC), IC11.4 (PRE), IC11.10 (PRE), IC11.12 (D), IC11.14 (VCC), IC16.16 (VCC), IC17.16 (VCC), IC18.14 (VCC), IC20.20 (VCC), IC22.14 (VCC), IC25.16 (VCC), IC29.16 (VCC), IC32.16 (VCC), IC36.6 (G1), IC36.16 (VCC), J3.2, J4.2, J5.2, J7.2; also elsewhere on the board
WRITING: IC6.2 (A), IC10.5 (Q); also elsewhere on the board

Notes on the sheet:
6601 DCMA - Use 601\\
6603 DMAR - Use 602\\
6605 DMAW - Use 604\\
6611 DCIM - Use 611\\
6612 DSAC - Use 612\\, but all skips are skip conditional with MB9\\
6615 DIML - Use DIML\\ (614\\ with MB10\\)
6616 DIMA - Use DIMA\\ (614\\ with MB10)
6621 DFSE - Use 621\\
6622 DFSC - Use 622\\
6623 DISK - Handled above.
6626 DMAC - Use 624\\
6641 DCXA - Use 641, MB9 chooses DAR clear vs AC clear
6643 DXAL - Use 642
6645 DXAC - Use 644, unless MB10
6646 DMMT - Handled above.
Posibus Connections
IOT Decode
Data Break
Hard-Wired 7750
Hard-Wired 3-Cycle
Break Request
Done Flag
Extended Address Gating
Read/Write State
Write Enable
Consider HC family.
checkinit polarity
BUGBUG: Errors should abort transfer.

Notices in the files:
projects/RF08/Old8x12/DF32-revision-B.brd:
DF32x4 Disk Emulator Rev. B (c)2003 CEMorris
